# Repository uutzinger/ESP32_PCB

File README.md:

# ESP32 PCBs

Designed with KiCad by Urs Utzinger, February - June 2026.

- Full size battery operated ESP32-S3-Mini
- Minimial size ESP32-S3.
- Minimal size ESP32-C6, low power.

Based on S3/C6-mini modules.

<table style="width:100%; table-layout:fixed;">
  <tr>
    <td valign="bottom" style="width:33.3%; text-align:center;">
      
      <br>
      <b>ESP32-S3-MINI-1</b>
      <ul style="text-align:left; margin:8px auto; max-width:90%; list-style:none; padding-left:0;">
        <li>📡 Antenna</li>
        <li>🔋 Battery management</li>
        <li>📊 Battery gauge</li>
        <li>⚡ Dual supply power (ext 5V or USB 5V) </li>
        <li>⇄ USB-C</li>
        <li>🔗 QWIIC</li>
        <li>🌈 RGB LED</li>
        <li>🌡 Temperature sensor</li>
        <li>🔘 Bootmode, Reset buttons</li>
      </ul>
    </td>
    <td valign="top" style="width:33.3%; text-align:center;">
      
      <br>
      <b>ESP32-S3-MINI-1U</b>
      <ul style="text-align:left; margin:8px auto; max-width:90%; list-style:none; padding-left:0;">
        <li>⚡ Dual supply power (external 5V or USB 5V)</li>
        <li>⇄ USB-C</li>
        <li>🔗 QWIIC</li>
        <li>🌈 RGB LED</li>
        <li>🌡 Temperature sensor</li>
        <li>🔘 Bootmode, Reset buttons</li>
      </ul>
    </td>
    <td valign="top" style="width:33.3%; text-align:center;">
      
      <br>
      <b>ESP32-C6-MINI-1</b>
      <ul style="text-align:left; margin:8px auto; max-width:90%; list-style:none; padding-left:0;">
        <li>📡 Antenna</li>
        <li>🔋 Battery management</li>
        <li>📊 Battery gauge</li>
        <li>⇄ USB-C</li>
        <li>🌡 Temperature sensor</li>
        <li>🫨 Acceleromter</li>
        <li>no Buttons
      </ul>
    </td>
  </tr>
</table>

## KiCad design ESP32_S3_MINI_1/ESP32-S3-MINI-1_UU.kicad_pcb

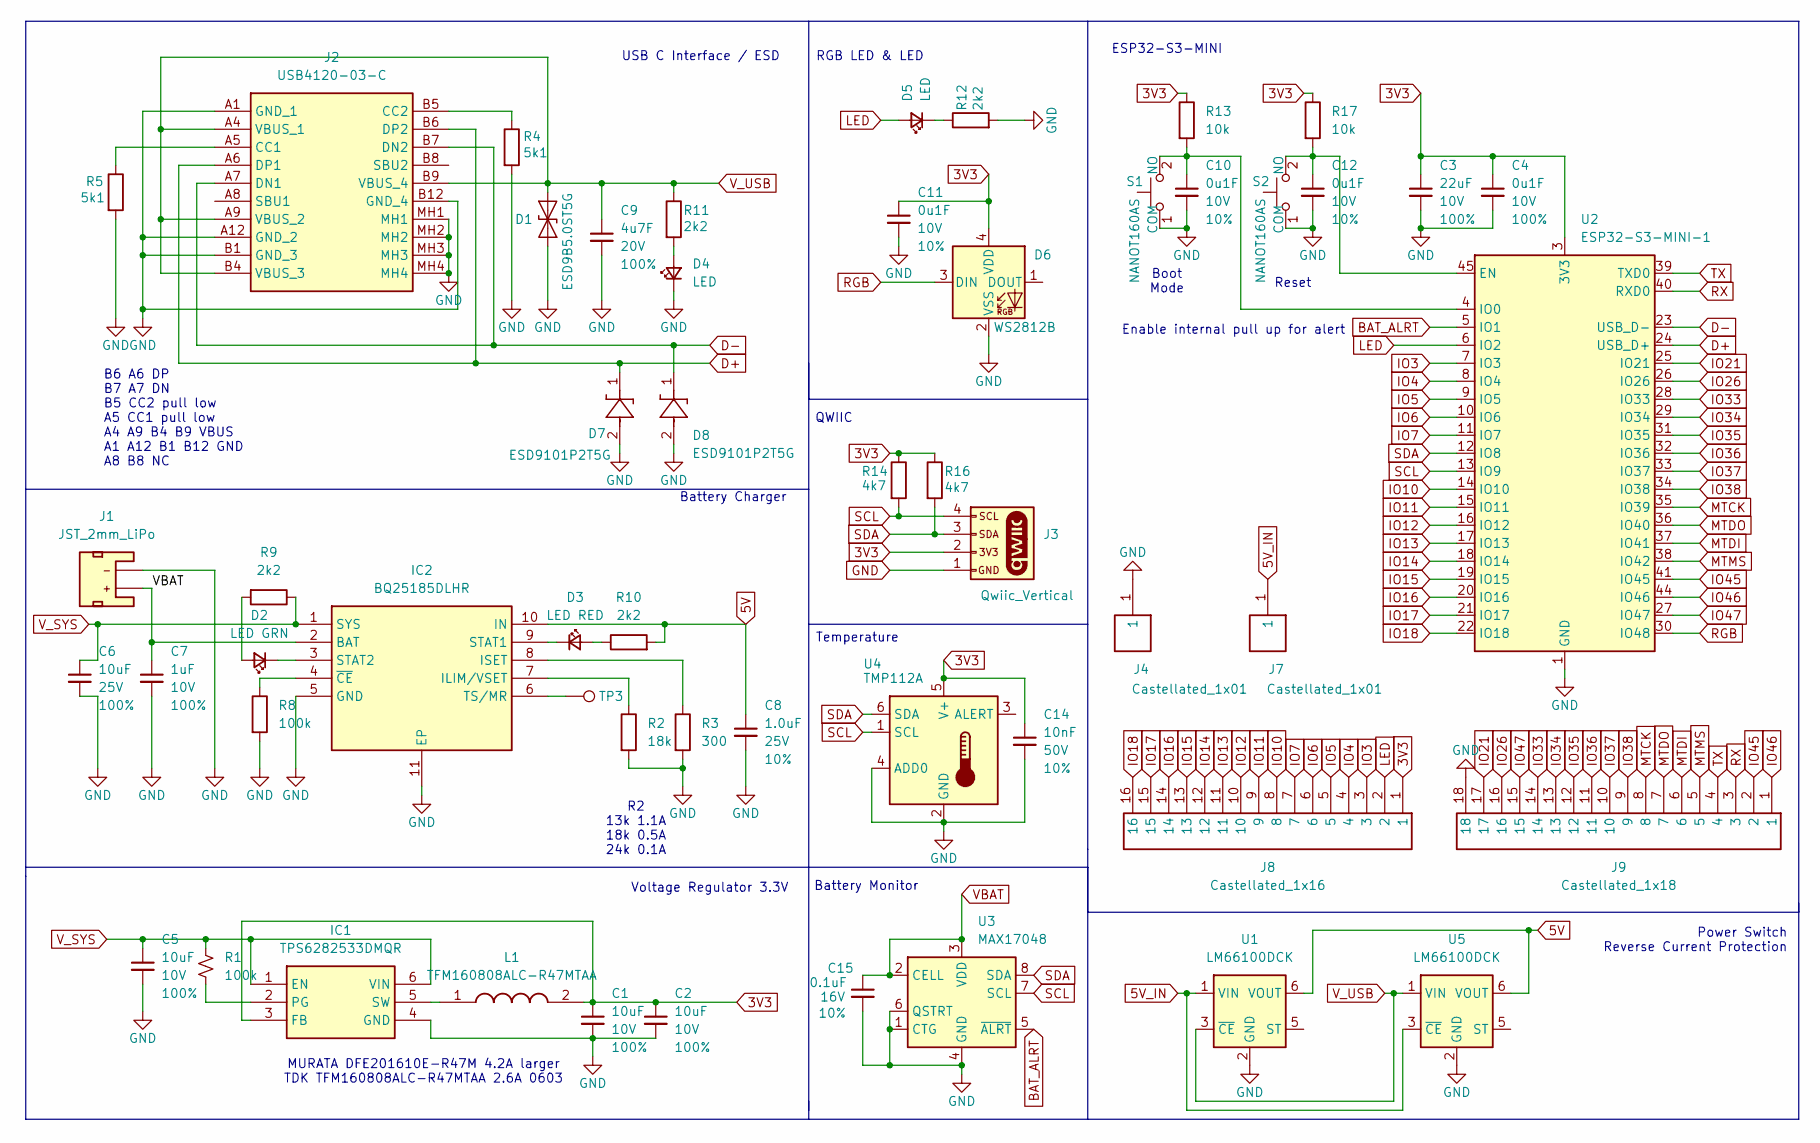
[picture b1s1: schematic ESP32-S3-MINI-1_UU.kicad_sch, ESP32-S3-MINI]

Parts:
C1, C2, C5: 10uF; C_0402_1005Metric; Voltage 10V; Tolerance 100%
C3: 22uF; C_0402_1005Metric; Voltage 10V; Tolerance 100%
C4: 0u1F; C_0402_1005Metric; Voltage 10V; Tolerance 100%
C6: 10uF; C_0402_1005Metric; Voltage 25V; Tolerance 100%
C7: 1uF; C_0402_1005Metric; Voltage 10V; Tolerance 100%
C8: 1.0uF; C_0402_1005Metric; Voltage 25V; Tolerance 10%
C9: 4u7F; C_0402_1005Metric; Voltage 20V; Tolerance 100%
C10, C11, C12: 0u1F; C_0402_1005Metric; Voltage 10V; Tolerance 10%
C14: 10nF; C_0402_1005Metric; Voltage 50V; Tolerance 10%
C15: 0.1uF; C_0402_1005Metric; Voltage 16V; Tolerance 10%
D1: ESD9B5.0ST5G; D_SOD-923
D2: LED GRN; LED_0402_1005Metric
D3: LED RED; LED_0402_1005Metric
D4, D5: LED; LED_0402_1005Metric
D6: WS2812B; WS2812_2020
D7, D8: ESD9101P2T5G; SODFL1006X40N; Manufacturer_Part_Number ESD9101P2T5G; Mouser Part Number 863-ESD9101P2T5G
IC1: TPS6282533DMQR; Manufacturer_Part_Number TPS6282533DMQR; Mouser Part Number 595-TPS6282533DMQR
IC2: BQ25185DLHR; SON40P220X200X80-11N; Manufacturer_Part_Number BQ25185DLHR; Mouser Part Number 595-BQ25185DLHR
J1: JST_2mm_LiPo; JST_1x02_P2.0mm_Horizontal_SMD
J2: USB4120-03-C; USB412003C; Manufacturer_Part_Number USB4120-03-C; Mouser Part Number 640-USB4120-03-C
J3: Qwiic_Vertical; JST_1x04_P1.0mm_Vertical_SMD
J4, J7: Castellated_1x01; Castellated_1x01_P2.54mm_D0.80mm
J8: Castellated_1x16; Castellated_1x16_P2.54mm_D0.80mm
J9: Castellated_1x18; Castellated_1x18_P2.54mm_D0.80mm
L1: TFM160808ALC-R47MTAA; INDC1608X75N; Manufacturer_Part_Number TFM160808ALC-R47MTAA; Mouser Part Number 810-TFM160808ALCR47A
R1, R8: 100k; R_0402_1005Metric
R2: 18k; R_0402_1005Metric
R3: 300; R_0402_1005Metric
R4, R5: 5k1; R_0402_1005Metric
R9, R10, R11, R12: 2k2; R_0402_1005Metric
R13, R17: 10k; R_0402_1005Metric
R14, R16: 4k7; R_0402_1005Metric
S1, S2: NANOT160AS; Mouser Part Number 611-NANOT160AS
TP3: TestPoint; TestPoint_Pad_1.0x1.0mm
U1, U5: LM66100DCK; SOT-363_SC-70-6
U2: ESP32-S3-MINI-1; ESP32-S2-MINI-1
U3: MAX17048; DFN-8_2x2mm_P0.5mm_EP1.2x0.8mm
U4: TMP112A; SOT-563

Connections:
3V3: C1.1, C2.1, C3.1, C4.1, C11.1, C14.1, D6.4 (VDD), IC1.3 (FB), J3.2, J8.1, L1.2, R13.1, R14.1, R16.1, R17.1, U2.3 (3V3), U4.5 (V+)
5V: C8.1, IC2.10 (IN), R10.2, U1.6 (VOUT), U5.6 (VOUT)
5V_IN: J7.1 (1_1), U1.1 (VIN), U5.3 (~CE)
BAT_ALRT: U2.5 (IO1), U3.5 (~ALRT)
D+: D7.1, J2.A6 (DP1), J2.B6 (DP2), U2.24 (USB_D+)
D-: D8.1, J2.A7 (DN1), J2.B7 (DN2), U2.23 (USB_D-)
GND: C1.2, C2.2, C3.2, C4.2, C5.2, C6.2, C7.2, C8.2, C9.2, C10.2, C11.2, C12.2, C14.2, C15.2, D1.2 (A2), D4.1 (K), D6.2 (VSS), D7.2, D8.2, IC1.4 (GND), IC2.5 (GND), IC2.11 (EP), J1.1 (-), J2.A1 (GND_1), J2.A12 (GND_2), J2.B1 (GND_3), J2.B12 (GND_4), J2.MH1, J2.MH2, J2.MH3, J2.MH4, J3.1, J4.1 (1_1), J9.18, R2.2, R3.2, R4.2, R5.2, R8.2, R12.2, S1.1 (COM), S2.1 (COM), U1.2 (GND), U2.1 (GND), U2.2 (GND), U2.42 (GND), U2.43 (GND), U2.46 (GND), U2.47 (GND), U2.48 (GND), U2.49 (GND), U2.50 (GND), U2.51 (GND), U2.52 (GND), U2.53 (GND), U2.54 (GND), U2.55 (GND), U2.56 (GND), U2.57 (GND), U2.58 (GND), U2.59 (GND), U2.60 (GND), U2.61 (GND), U2.62 (GND), U2.63 (GND), U2.64 (GND), U2.65 (GND), U3.1 (CTG), U3.4 (GND), U3.6 (QSTRT), U3.9 (GND), U4.2 (GND), U4.4 (ADD0), U5.2 (GND)
IO3: J8.3, U2.7 (IO3)
IO4: J8.4, U2.8 (IO4)
IO5: J8.5, U2.9 (IO5)
IO6: J8.6, U2.10 (IO6)
IO7: J8.7, U2.11 (IO7)
IO10: J8.8, U2.14 (IO10)
IO11: J8.9, U2.15 (IO11)
IO12: J8.10, U2.16 (IO12)
IO13: J8.11, U2.17 (IO13)
IO14: J8.12, U2.18 (IO14)
IO15: J8.13, U2.19 (IO15)
IO16: J8.14, U2.20 (IO16)
IO17: J8.15, U2.21 (IO17)
IO18: J8.16, U2.22 (IO18)
IO21: J9.17, U2.25 (IO21)
IO26: J9.16, U2.26 (IO26)
IO33: J9.14, U2.28 (IO33)
IO34: J9.13, U2.29 (IO34)
IO35: J9.12, U2.31 (IO35)
IO36: J9.11, U2.32 (IO36)
IO37: J9.10, U2.33 (IO37)
IO38: J9.9, U2.34 (IO38)
IO45: J9.2, U2.41 (IO45)
IO46: J9.1, U2.44 (IO46)
IO47: J9.15, U2.27 (IO47)
LED: D5.2 (A), J8.2, U2.6 (IO2)
MTCK: J9.8, U2.35 (IO39)
MTDI: J9.6, U2.37 (IO41)
MTDO: J9.7, U2.36 (IO40)
MTMS: J9.5, U2.38 (IO42)
unnamed: D2.2 (A), R9.2
unnamed: D2.1 (K), IC2.3 (STAT2)
unnamed: D3.2 (A), R10.1
unnamed: D3.1 (K), IC2.9 (STAT1)
unnamed: D4.2 (A), R11.2
unnamed: D5.1 (K), R12.1
unnamed: IC1.2 (PG), R1.1
unnamed: IC1.5 (SW), L1.1
unnamed: IC2.7 (ILIM/VSET), R2.1
unnamed: IC2.8 (ISET), R3.1
unnamed: IC2.6 (TS/MR), TP3.1 (1_1)
unnamed: IC2.4 (~CE), R8.1
unnamed: J2.A5 (CC1), R5.1
unnamed: J2.B5 (CC2), R4.1
unnamed: C10.1, R13.2, S1.2 (NO), U2.4 (IO0)
unnamed: C12.1, R17.2, S2.2 (NO), U2.45 (EN)
RGB: D6.3 (DIN), U2.30 (IO48)
RX: J9.3, U2.40 (RXD0)
SCL: J3.4, R14.2, U2.13 (IO9), U3.7 (SCL), U4.1 (SCL)
SDA: J3.3, R16.2, U2.12 (IO8), U3.8 (SDA), U4.6 (SDA)
TX: J9.4, U2.39 (TXD0)
VBAT: C7.1, C15.1, IC2.2 (BAT), J1.2 (+), U3.2 (CELL), U3.3 (VDD)
V_SYS: C5.1, C6.1, IC1.1 (EN), IC1.6 (VIN), IC2.1 (SYS), R1.2, R9.1
V_USB: C9.1, D1.1 (A1), J2.A4 (VBUS_1), J2.A9 (VBUS_2), J2.B4 (VBUS_3), J2.B9 (VBUS_4), R11.1, U1.3 (~CE), U5.1 (VIN)

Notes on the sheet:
Voltage Regulator 3.3V
Boot Mode
ESP32-S3-MINI
Battery Monitor
Power Switch Reverse Current Protection
MURATA DFE201610E-R47M 4.2A larger TDK TFM160808ALC-R47MTAA 2.6A 0603
Temperature
RGB LED & LED
Reset
R2 13k 1.1A 18k 0.5A 24k 0.1A
Battery Charger
Enable internal pull up for alert
B6 A6 DP B7 A7 DN B5 CC2 pull low A5 CC1 pull low A4 A9 B4 B9 VBUS A1 A12 B1 B12 GND A8 B8 NC
USB C Interface / ESD
QWIIC

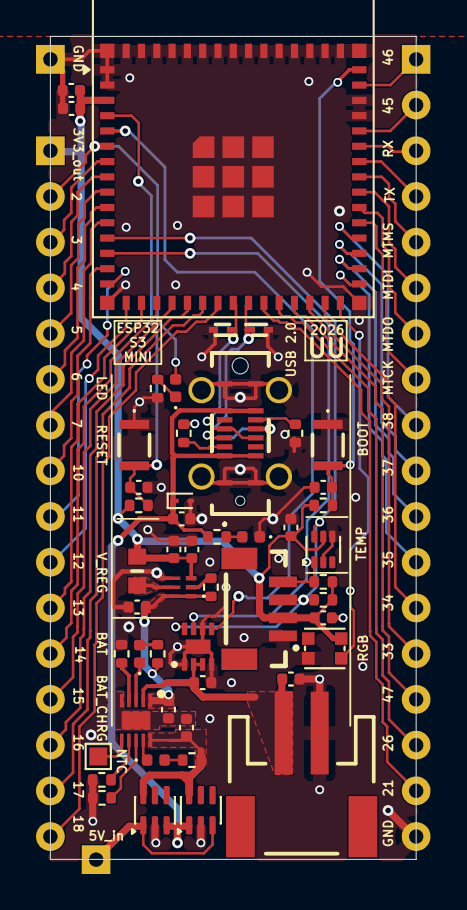
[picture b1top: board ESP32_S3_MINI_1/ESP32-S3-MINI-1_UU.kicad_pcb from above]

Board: 2 copper layers, 20.3 x 45.7 mm, 54 parts (0 on the bottom side), 61 nets.

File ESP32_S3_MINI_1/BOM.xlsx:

Id | Designator | Footprint | Quantity | Item | Manufacturer | Mfg Part # | Description/Value | Part # LCSC | LCSC | Cost LCSC |  | Part # Mouser | Mouser website | Cost Mouser
1 | C11,C12,C10,C15,C4 | C_0402_1005Metric | 5 | Capacitor | muRata | GRM155R71A104KA01D | 0u1F | C71687 | https://www.lcsc.com/product-detail/C71687.html?s_z=n_C71687 | 0.32 | 1.6
2 | C14 | C_0402_1005Metric | 1 | Capacitor | YAGEO | CC0402KRX7R6BB103 | 10nF | C541371 | https://www.lcsc.com/product-detail/C541371.html?s_z=n_C541371 | 0.13 | 0.13
3 | C3 | C_0402_1005Metric | 1 | Capacitor | muRata | GRM158R61A226ME15D | 22uF | C3845593 | https://www.lcsc.com/product-detail/C3845593.html?s_z=n_C3845593 | 0.57 | 0.57
4 | C5,C1,C2,C6 | C_0402_1005Metric | 4 | Capacitor | muRata | GRM155R61A106ME44D | 10uF | C77000 | https://www.lcsc.com/product-detail/C77000.html?s_z=n_C77000 | 0.58 | 2.32
5 | C7,C8 | C_0402_1005Metric | 2 | Capacitor | muRata | GCM155C71A105KE38D | 1uF | C126521 | https://www.lcsc.com/product-detail/C126521.html?s_z=n_C126521 | 0.96 | 1.92
6 | C9 | C_0402_1005Metric | 1 | Capacitor | muRata | GRM155R61A475KEAAD | 4u7F | C77004 | https://www.lcsc.com/product-detail/C77004.html?s_z=n_C77004 | 0.81 | 0.81
7 | D1 | D_SOD-923 | 1 | V_USB ESD | onSemi | ESD9B5.0ST5G | ESD9B5.0ST5G | C111566 | https://www.lcsc.com/product-detail/C111566.html?s_z=n_C111566 | 0.04 | 0.04 | 863-ESD9B5.0ST5G | https://www.mouser.com/ProductDetail/onsemi/ESD9B5.0ST5G?qs=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 | 0.1
8 | D2 | LED_0402_1005Metric | 1 | LED | Vishay | VLMG1500-GS08 | LED GRN | C511404 | https://www.lcsc.com/product-detail/C511404.html?s_z=n_C511404 | 0.19 | 0.19 | 78-VLMG1500-GS08 | https://www.mouser.com/ProductDetail/Vishay-Semiconductors/V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 | 0.34
9 | D3 | LED_0402_1005Metric | 1 | LED | Vishay | VLMS1500-GS08 | LED RED | C511370 | https://www.lcsc.com/product-detail/C511370.html?s_z=n_C511370 | 0.17 | 0.17 | 78-VLMS1500-GS08 | https://www.mouser.com/ProductDetail/Vishay-Semiconductors/V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 | 0.24
10 | D4,D5 | LED_0402_1005Metric | 2 | LED | Vishay | VLMB1500-GS08 | LED BLUE | C511042 | https://www.lcsc.com/product-detail/C511042.html?s_z=n_C511042 | 0.2 | 0.4 | 78-VLMB1500-GS08 | https://www.mouser.com/ProductDetail/Vishay-Semiconductors/V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 | 0.27
11 | D6 | WS2812_2020 | 1 | RGB LED | Worldsemi | WS2812B-2020 | WS2812B | C965555 | https://www.lcsc.com/product-detail/C965555.html?s_z=n_C965555 | 0.45 | 0.45
12 | D7,D8 | D_SOD-923 | 2 | USB ESD | Onsemi | ESD9101P2T5G | ESD9101P2T5G | C41348159 | https://www.lcsc.com/product-detail/C41348159.html?s_z=n_ESD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 | 0.56 | 1.12 | 863-ESD9101P2T5G | https://www.mouser.com/ProductDetail/onsemi/ESD9101P2T5G?qs=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 | 0.26
13 | IC1 | TPS6282533DMQR | 1 | Volt Regulator | TI | TPS6282533DMQR | TPS6282533DMQR | C3189971 | https://www.lcsc.com/product-detail/C3189971.html?s_z=n_C3189971 | 1.17 | 1.17 | 595-TPS6282533DMQR | https://www.mouser.com/ProductDetail/Texas-Instruments/TPS62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 | 1.25
14 | IC2 | SON40P220X200X80-11N | 1 | Bat Charger | TI | BQ25185DLHR | BQ25185DLHR | C19725033 | https://www.lcsc.com/product-detail/C19725033.html?s_z=n_C19725033 | 1.9 | 1.9 | 595-BQ25185DLHR | https://www.mouser.com/ProductDetail/Texas-Instruments/BQ251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 | 2.03
15 | J1 | JST_1x02_P2.0mm_Horizontal_SMD | 1 | Connector | JST | JST S2B-PH-SM4-TB | JST_2mm_LiPo, SMF, right angle | C295747 | https://www.lcsc.com/product-detail/C295747.html?s_z=n_C295747 | 0.2 | 0.2 | 306-S2BPHSM4TBLFSN | https://www.mouser.com/ProductDetail/JST-Commercial/S2B-PH-S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 | 0.49
16 | J2 | USB412003C | 1 | Connector | GCT | USB4120-03-C | USB4120-03-C | C3445864 | https://www.lcsc.com/product-detail/C3445864.html?s_z=n_C3445864 | 1.31 | 1.31 | 640-USB4120-03-C | https://www.mouser.com/ProductDetail/GCT/USB4120-03-C?qs=KUo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 | 0.86
17 | J3 | JST_1x04_P1.0mm_Vertical_SMD | 1 | Connector | BOOMELE | 1.0T-4PLTPZ | Qwiic_Vertical | C2974722 | https://www.lcsc.com/product-detail/C2974722.html | 0.65 | 0.65
18 | J7,J4 | Castellated_1x01_P2.54mm_D0.80mm | 1 | Connector | D.N.P. | D.N.P. | Castellated_1x01 |  | Do No Populate
19 | J8 | Castellated_1x16_P2.54mm_D0.80mm | 1 | Connector | D.N.P. | D.N.P. | Castellated_1x16 |  | Do No Populate
20 | J9 | Castellated_1x18_P2.54mm_D0.80mm | 1 | Connector | D.N.P. | D.N.P. | Castellated_1x18 |  | Do No Populate
21 | L1 | C_0603 | 1 | Inductor | TDK | TFM160808ALC-R47MTAA | TFM160808ALC-R47MTAA | C695609 | https://www.lcsc.com/product-detail/C695609.html?s_z=n_C695609 | 0.13 | 0.13 | 810-TFM160808ALCR47A | https://www.mouser.com/ProductDetail/TDK/TFM160808ALC-R47MTA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 | 0.25
22 | R1,R8 | R_0402_1005Metric | 2 | Resistor | YAGEO | RC0402FR-07100KL | 100k | C60491 | https://www.lcsc.com/product-detail/C60491.html?s_z=n_C60491 | 0.08 | 0.16
23 | R14,R16 | R_0402_1005Metric | 2 | Resistor | YAGEO | RC0402FR-074K7L | 4k7 | C105871 | https://www.lcsc.com/product-detail/C105871.html?s_z=n_C105871 | 0.08 | 0.16
24 | R15 | R_0402_1005Metric | 1 | Resistor | YAGEO | RC0402FR-07330RL | 330 | C105875 | https://www.lcsc.com/product-detail/C105875.html?s_z=n_C105875 | 0.08 | 0.08
25 | R2 | R_0402_1005Metric | 1 | Resistor | YAGEO | RC0402FR-0718KL | 18k | C138044 | https://www.lcsc.com/product-detail/C138044.html?s_z=n_C138044 | 0.08 | 0.08
26 | R3 | R_0402_1005Metric | 1 | Resistor | YAGEO | RC0402FR-07300RL | 300 | C138010 | https://www.lcsc.com/product-detail/C138010.html?s_z=n_C138010 | 0.08 | 0.08
27 | R4,R5 | R_0402_1005Metric | 2 | Resistor | YAGEO | RC0402FR-075K1L | 5k1 | C105872 | https://www.lcsc.com/product-detail/C105872.html?s_z=n_C105872 | 0.08 | 0.16
28 | R9,R12,R10,R11 | R_0402_1005Metric | 4 | Resistor | YAGEO | RC0402FR-072K2L | 2k2 | C114762 | https://www.lcsc.com/product-detail/C114762.html?s_z=n_C114762 | 0.09 | 0.36
29 | S1,S2 | NANOT160AS | 2 | Micro Switch | C&K | NANOT160AS | NANOT160AS | C2760981 | https://www.lcsc.com/product-detail/C2760981.html?s_z=n_C2760981 | 1.72 | 3.44 | 611-NANOT160AS | https://www.mouser.com/ProductDetail/CK/NANOT160AS?qs=OlC7Aq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 | 0.4
30 | R13,R17 | R_0402_1005Metric | 2 | Resistor | YAGEO | RC0402FR-0710KL | 10k | C60490 | https://www.lcsc.com/product-detail/C60490.html?s_z=n_C60490 | 0.08 | 0.16
31 | TH1 | R_0402_1005Metric | 1 | Thermistor | MURATA | NCP15XH103F03RC | 10k NTC | C77131 | https://www.lcsc.com/product-detail/C77131.html?s_z=n_C77131 | 0.01 | 0.01
32 | U2 | ESP32-S2-MINI-1 SMD | 1 | MCU Module | Espressif | ESP32-S3-MINI-1-N8 | ESP32 S3 Mini 1 8MB Flash | C2913206 | https://www.lcsc.com/product-detail/C2913206.html?s_z=n_C2913206 | 4.6185 | 4.6185
33 | U3 | DFN-8_2x2mm_P0.5mm_EP1.2x0.8mm | 1 | Bat Gauge | Maxim | MAXIM MAX17048G+T10 | MAX17048 | C2682616 | https://www.lcsc.com/product-detail/C2682616.html?s_z=n_C2682616 | 2.66 | 2.66 | 700-MAX17048G+T10 | https://www.mouser.com/ProductDetail/Analog-Devices-Maxim-In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 | 5.77
34 | U4 | SOT-563 | 1 | Temp Sensor | Texas Instruments | TMP102AIDRLR | TMP102 | C99269 | https://www.lcsc.com/product-detail/C99269.html?s_z=n_C99269 | 0.22 | 0.22 | 595-TMP102AQDRLRQ1 | https://www.mouser.com/ProductDetail/Texas-Instruments/TMP10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 | 1.52
35 | U5,U1 | SOT-363_SC-70-6 | 2 | Ideal Diode | Texas Instruments | LM66100DCK | Ideal Diode, Input Polarity Prot. | C2869734 | https://www.lcsc.com/product-detail/C2869734.html?s_z=n_C2869734 | 0.88 | 1.76 | 595-LM66100DCKT | https://www.mouser.com/ProductDetail/Texas-Instruments/LM661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 | 0.85
 |  |  |  |  |  |  |  |  |  |  | 29.0285

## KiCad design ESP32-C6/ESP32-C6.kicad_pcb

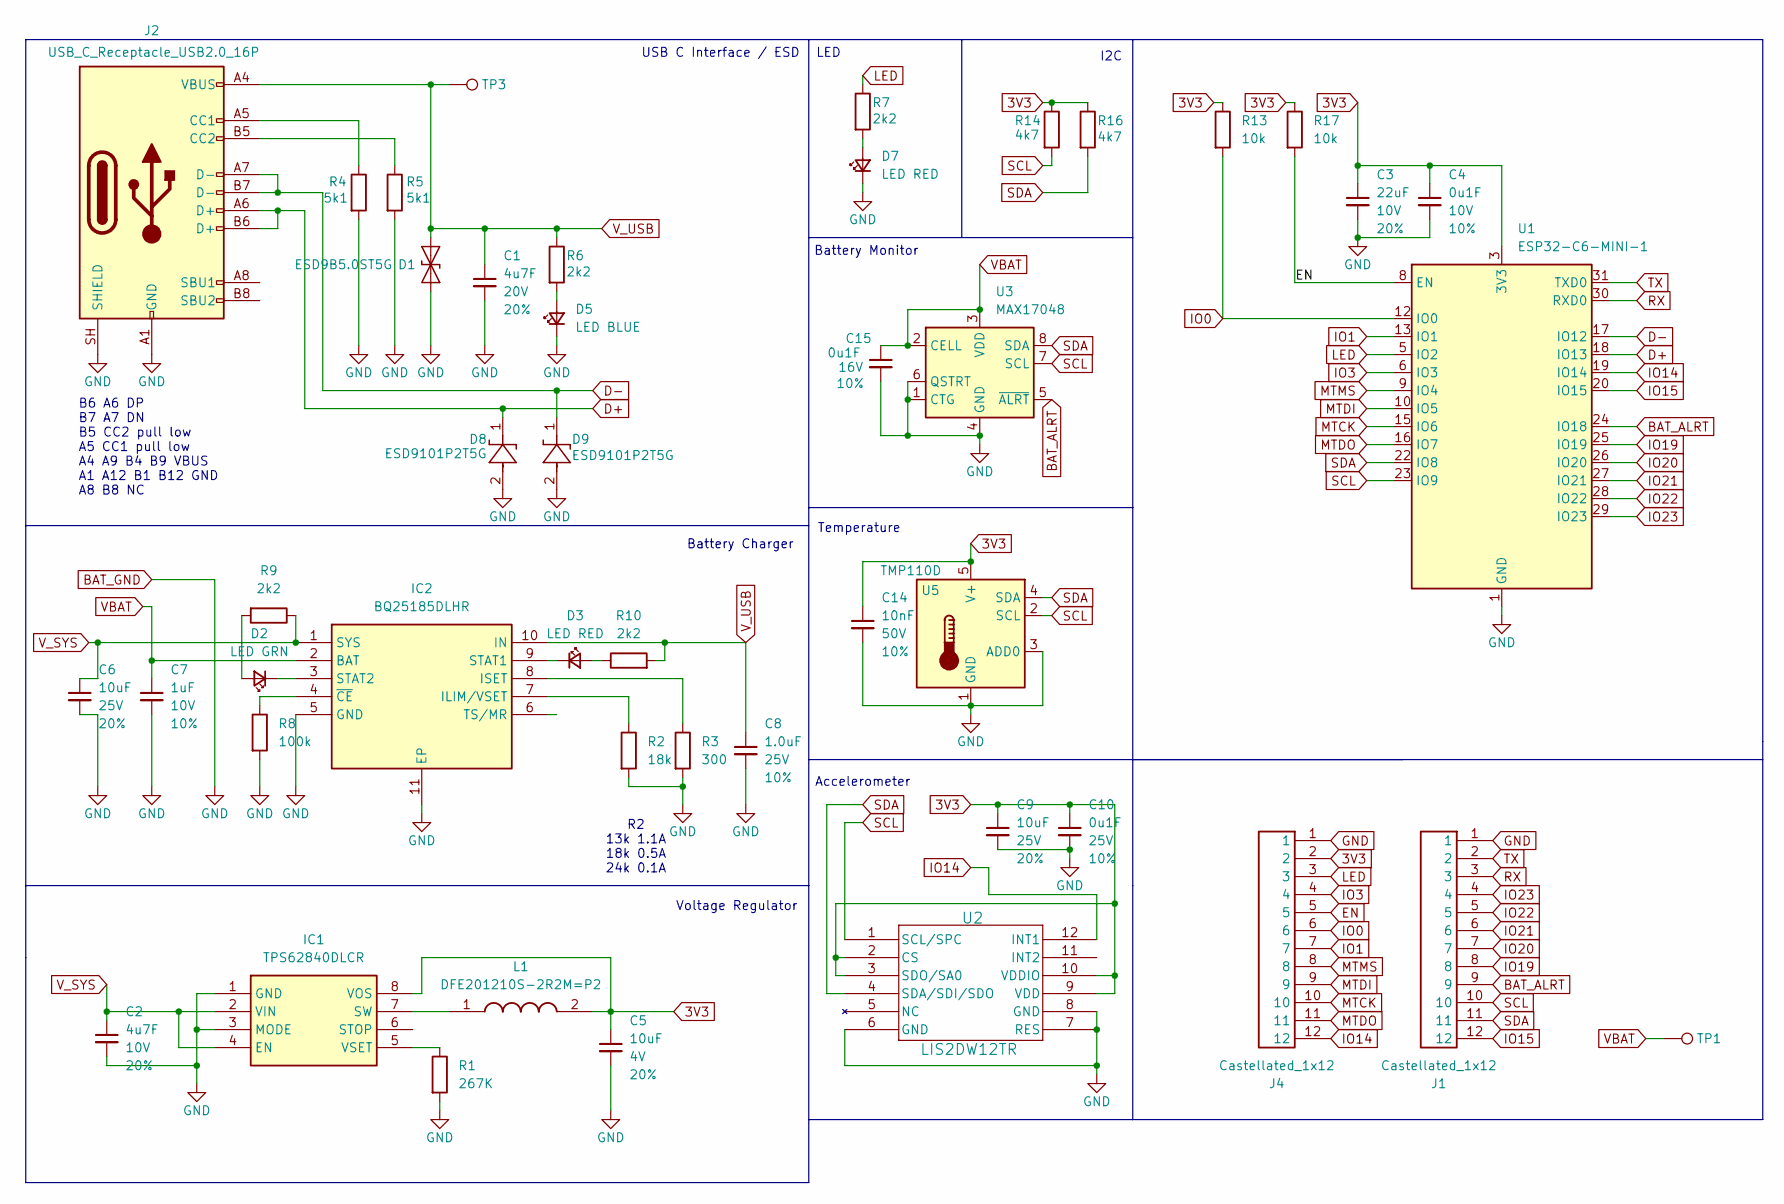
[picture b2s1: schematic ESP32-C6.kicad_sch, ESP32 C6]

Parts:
C1: 4u7F; C_0402_1005Metric; Voltage 20V; Tolerance 20%
C2: 4u7F; C_0402_1005Metric; Voltage 10V; Tolerance 20%
C3: 22uF; C_0402_1005Metric; Voltage 10V; Tolerance 20%
C4: 0u1F; C_0402_1005Metric; Voltage 10V; Tolerance 10%
C5: 10uF; C_0402_1005Metric; Voltage 4V; Tolerance 20%
C6, C9: 10uF; C_0402_1005Metric; Voltage 25V; Tolerance 20%
C7: 1uF; C_0402_1005Metric; Voltage 10V; Tolerance 10%
C8: 1.0uF; C_0402_1005Metric; Voltage 25V; Tolerance 10%
C10: 0u1F; C_0402_1005Metric; Voltage 25V; Tolerance 10%
C14: 10nF; C_0201_0603Metric; Voltage 50V; Tolerance 10%
C15: 0u1F; C_0402_1005Metric; Voltage 16V; Tolerance 10%
D1: ESD9B5.0ST5G; D_SOD-923
D2: LED GRN; LED_0402_1005Metric
D3, D7: LED RED; LED_0402_1005Metric
D5: LED BLUE; LED_0402_1005Metric
D8, D9: ESD9101P2T5G; SODFL1006X40N; Manufacturer_Part_Number ESD9101P2T5G; Mouser Part Number 863-ESD9101P2T5G
IC1: TPS62840DLCR; SON50P150X200X100-8N-D; Manufacturer_Part_Number TPS62840DLCR; Mouser Part Number 595-TPS62840DLCR
IC2: BQ25185DLHR; SON40P220X200X80-11N; Manufacturer_Part_Number BQ25185DLHR; Mouser Part Number 595-BQ25185DLHR
J1, J4: Castellated_1x12; Castellated_1x12_P2.54mm_D0.80mm
J2: USB_C_Receptacle_USB2.0_16P; USB_C_Receptacle_GCT_USB4105-xx-A_16P_TopMnt_Horizontal
L1: DFE201210S-2R2M=P2; DFE201210S1R0MP2; Manufacturer_Part_Number DFE201210S-2R2M=P2; Mouser Part Number 81-DFE201210S-2R2MP2
R1: 267K; R_0402_1005Metric
R2: 18k; R_0402_1005Metric
R3: 300; R_0402_1005Metric
R4, R5: 5k1; R_0402_1005Metric
R6, R7, R9, R10: 2k2; R_0402_1005Metric
R8: 100k; R_0402_1005Metric
R13, R17: 10k; R_0402_1005Metric
R14, R16: 4k7; R_0402_1005Metric
TP1, TP3: TestPoint; TestPoint_Pad_1.5x1.5mm
U1: ESP32-C6-MINI-1
U2: LIS2DW12TR; LGA-12_2X2X0P7_STM
U3: MAX17048; DFN-8_2x2mm_P0.5mm_EP1.2x0.8mm
U5: TMP110D; Texas_X2SON-5_0.8x0.8mm_P0.48mm

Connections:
3V3: C3.1, C4.1, C5.1, C9.1, C10.1, C14.1, IC1.8 (VOS), J4.2, L1.2, R13.1, R14.1, R16.1, R17.1, U1.3 (3V3), U2.2 (CS), U2.3 (SDO/SA0), U2.9 (VDD), U2.10 (VDDIO), U5.5 (V+)
BAT_ALRT: J1.9, U1.24 (IO18), U3.5 (~ALRT)
BAT_GND: C1.2, C2.2, C3.2, C4.2, C5.2, C6.2, C7.2, C8.2, C9.2, C10.2, C14.2, C15.2, D1.2 (A2), D5.1 (K), D7.1 (K), D8.2, D9.2, IC1.1 (GND), IC1.3 (MODE), IC2.5 (GND), IC2.11 (EP), J1.1, J2.A1 (GND), J2.A12 (GND), J2.B1 (GND), J2.B12 (GND), J2.SH (SHIELD), J4.1, R1.2, R2.2, R3.2, R4.2, R5.2, R8.2, U1.1 (GND), U1.2 (GND), U1.11 (GND), U1.14 (GND), U1.36 (GND), U1.37 (GND), U1.38 (GND), U1.39 (GND), U1.40 (GND), U1.41 (GND), U1.42 (GND), U1.43 (GND), U1.44 (GND), U1.45 (GND), U1.46 (GND), U1.47 (GND), U1.48 (GND), U1.49 (GND), U1.50 (GND), U1.51 (GND), U1.52 (GND), U1.53 (GND), U2.6 (GND), U2.7 (RES), U2.8 (GND), U3.1 (CTG), U3.4 (GND), U3.6 (QSTRT), U3.9 (GND), U5.1 (GND), U5.3 (ADD0)
D+: D8.1, J2.A6 (D+), J2.B6 (D+), U1.18 (IO13)
D-: D9.1, J2.A7 (D-), J2.B7 (D-), U1.17 (IO12)
EN: J4.5, R17.2, U1.8 (EN)
IO0: J4.6, R13.2, U1.12 (IO0)
IO1: J4.7, U1.13 (IO1)
IO3: J4.4, U1.6 (IO3)
IO14: J4.12, U1.19 (IO14), U2.12 (INT1)
IO15: J1.12, U1.20 (IO15)
IO19: J1.8, U1.25 (IO19)
IO20: J1.7, U1.26 (IO20)
IO21: J1.6, U1.27 (IO21)
IO22: J1.5, U1.28 (IO22)
IO23: J1.4, U1.29 (IO23)
LED: J4.3, R7.1, U1.5 (IO2)
MTCK: J4.10, U1.15 (IO6)
MTDI: J4.9, U1.10 (IO5)
MTDO: J4.11, U1.16 (IO7)
MTMS: J4.8, U1.9 (IO4)
unnamed: D2.2 (A), R9.2
unnamed: D2.1 (K), IC2.3 (STAT2)
unnamed: D3.2 (A), R10.1
unnamed: D3.1 (K), IC2.9 (STAT1)
unnamed: D5.2 (A), R6.2
unnamed: D7.2 (A), R7.2
unnamed: IC1.7 (SW), L1.1
unnamed: IC1.5 (VSET), R1.1
unnamed: IC2.7 (ILIM/VSET), R2.1
unnamed: IC2.8 (ISET), R3.1
unnamed: IC2.4 (~CE), R8.1
unnamed: J2.A5 (CC1), R4.1
unnamed: J2.B5 (CC2), R5.1
RX: J1.3, U1.30 (RXD0)
SCL: J1.10, R14.2, U1.23 (IO9), U2.1 (SCL/SPC), U3.7 (SCL), U5.2 (SCL)
SDA: J1.11, R16.2, U1.22 (IO8), U2.4 (SDA/SDI/SDO), U3.8 (SDA), U5.4 (SDA)
TX: J1.2, U1.31 (TXD0)
VBAT: C7.1, C15.1, IC2.2 (BAT), TP1.1 (1_1), U3.2 (CELL), U3.3 (VDD)
V_SYS: C2.1, C6.1, IC1.2 (VIN), IC1.4 (EN), IC2.1 (SYS), R9.1
V_USB: C1.1, C8.1, D1.1 (A1), IC2.10 (IN), J2.A4 (VBUS), J2.A9 (VBUS), J2.B4 (VBUS), J2.B9 (VBUS), R6.1, R10.2, TP3.1 (1_1)

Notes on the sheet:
Accelerometer
B6 A6 DP B7 A7 DN B5 CC2 pull low A5 CC1 pull low A4 A9 B4 B9 VBUS A1 A12 B1 B12 GND A8 B8 NC
Battery Monitor
Voltage Regulator
I2C
LED
Battery Charger
Temperature
R2 13k 1.1A 18k 0.5A 24k 0.1A
USB C Interface / ESD

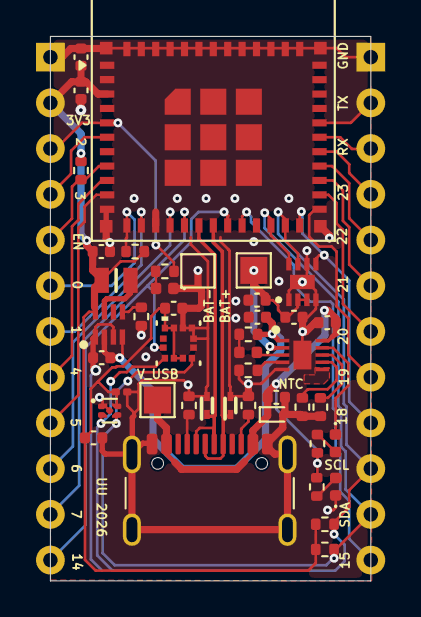
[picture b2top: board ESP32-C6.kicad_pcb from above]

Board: 2 copper layers, 17.8 x 30.2 mm, 45 parts (0 on the bottom side), 41 nets.

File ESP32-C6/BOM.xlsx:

Item # | *Designator | *Package/Footprint | *Qty | Item | Manufacturer | *Mfg Part # | Description / Value | Part # LCSC | LCSC Weblink | LSCS $ | Cost LCSC | Part # Mouser | Mouser Weblink | Mouser $
 | C1,C2 | C_0402_1005Metric | 2 | Capacitor | muRata | GRM155R61A475KEAAD | 4u7F | C77004 | https://www.lcsc.com/product-detail/C77004.html?s_z=n_C77004 | 0.81 | 1.62
 | C14 | C_0201_0603Metric | 1 | Capacitor | muRata | GRM033R71E103KE14D | 10nF | C85930 | https://www.lcsc.com/product-detail/C85930.html | 0.22 | 0.22
 | C10,C15,C4 | C_0402_1005Metric | 2 | Capacitor | muRata | GRM155R71H104KE14 | 0u1F | C77020 | https://www.lcsc.com/product-detail/C77020.htm | 0.33 | 0.66
 | C3 | C_0402_1005Metric | 1 | Capacitor | muRata | GRM158R61A226ME15D | 22uF | C3845593 | https://www.lcsc.com/product-detail/C3845593.html?s_z=n_C3845593 | 0.57 | 0.57
 | C6,C5, C9 | C_0402_1005Metric | 3 | Capacitor | muRata | GRM155R61A106ME44D | 10uF | C77000 | https://www.lcsc.com/product-detail/C77000.html?s_z=n_C77000 | 0.58 | 1.74
 | C7,C8 | C_0402_1005Metric | 2 | Capacitor | muRata | GRM155R61E105KA12 | 1uF | C77009 | https://www.lcsc.com/product-detail/C77009.html | 0.69 | 1.38
 | D1 | D_SOD-923 | 1 | ESD9B5.0ST5G | onSemi | ESD9B5.0ST5G | ESD9B5.0ST5G | C111566 | https://www.lcsc.com/product-detail/C111566.html?s_z=n_C111566 | 0.04 | 0.04
 | D2 | LED_0402_1005Metric | 1 | LED GRN | TOGIALED | TJ-S1005CL4T5ALC2G-A5 | LED GREEN | C917188 | https://www.lcsc.com/product-detail/C917188.html | 0.66
 | D3 | LED_0402_1005Metric | 1 | LED RED | TOGIALED | TJ-S1005SW4TGLC2R-A5 | LED RED | C273598 | https://www.lcsc.com/product-detail/C273598.html | 0.41 | 0.41
 | D7 | LED_0402_1005Metric | 1 | LED WHITE | TOGIALED | TJ-S1005CL4T5ALC3D | LED WHITE | C917191 | https://www.lcsc.com/product-detail/C917191.html | 0.48
 | D5 | LED_0402_1005Metric | 1 | LED BLUE | Vishay | VLMB1500-GS08 | LED BLUE | C511042 | https://www.lcsc.com/product-detail/C511042.html?s_z=n_C511042 | 0.2
 | D8,D9 | D_SOD-923 | 2 | ESD9101P2T5G | onSemi | ESD9101P2T5G | ESD9101P2T5G | C41348159 | https://www.lcsc.com/product-detail/C41348159.html?s_z=n_ESD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 | 0.56
 | IC1 | SON50P150X200X100-8N-D | 1 | TPS62840DLCR
 | IC2 | SON40P220X200X80-11N | 1 | BQ25185DLHR
 | J1,J4 | Castellated_1x12_P2.54mm_D0.80mm | 2 | Castellated_1x12
 | J2 |  | 1 | USB_C_Receptacle_USB2.0_16P |  | USB_C_Receptacle_GCT_USB4105-xx-A_16P_TopMnt_Horizontal
 | L1 | DFE201210S1R0MP2 | 1 | Inductor |  | DFE201210S-2R2M=P2
 | R1 | R_0402_1005Metric | 1 | 267K
 | R14,R16 | R_0402_1005Metric | 2 | 4k7
 | R17,R13 | R_0402_1005Metric | 2 | 10k
 | R2 | R_0402_1005Metric | 1 | 18k
 | R3 | R_0402_1005Metric | 1 | 300
 | R5,R4 | R_0402_1005Metric | 2 | 5k1
 | R7,R10,R6,R9 | R_0402_1005Metric | 4 | 2k2
 | R8 | R_0402_1005Metric | 1 | 100k
28 | TP1 | TestPoint_Pad_1.5x1.5mm | 1 | TestPoint
29 | TP3 | TestPoint_Pad_1.5x1.5mm | 1 | TestPoint
 | U1 | ESP32-C6-MINI-1 | 1 | MCU Module | Espressif Systems
 | U2 | LGA-12_2X2X0P7_STM | 1 | LIS2DW12TR
 | U3 | DFN-8_2x2mm_P0.5mm_EP1.2x0.8mm | 1 | MAX17048
 | U5 | Texas_X2SON-5_0.8x0.8mm_P0.48mm | 1 | TMP110D

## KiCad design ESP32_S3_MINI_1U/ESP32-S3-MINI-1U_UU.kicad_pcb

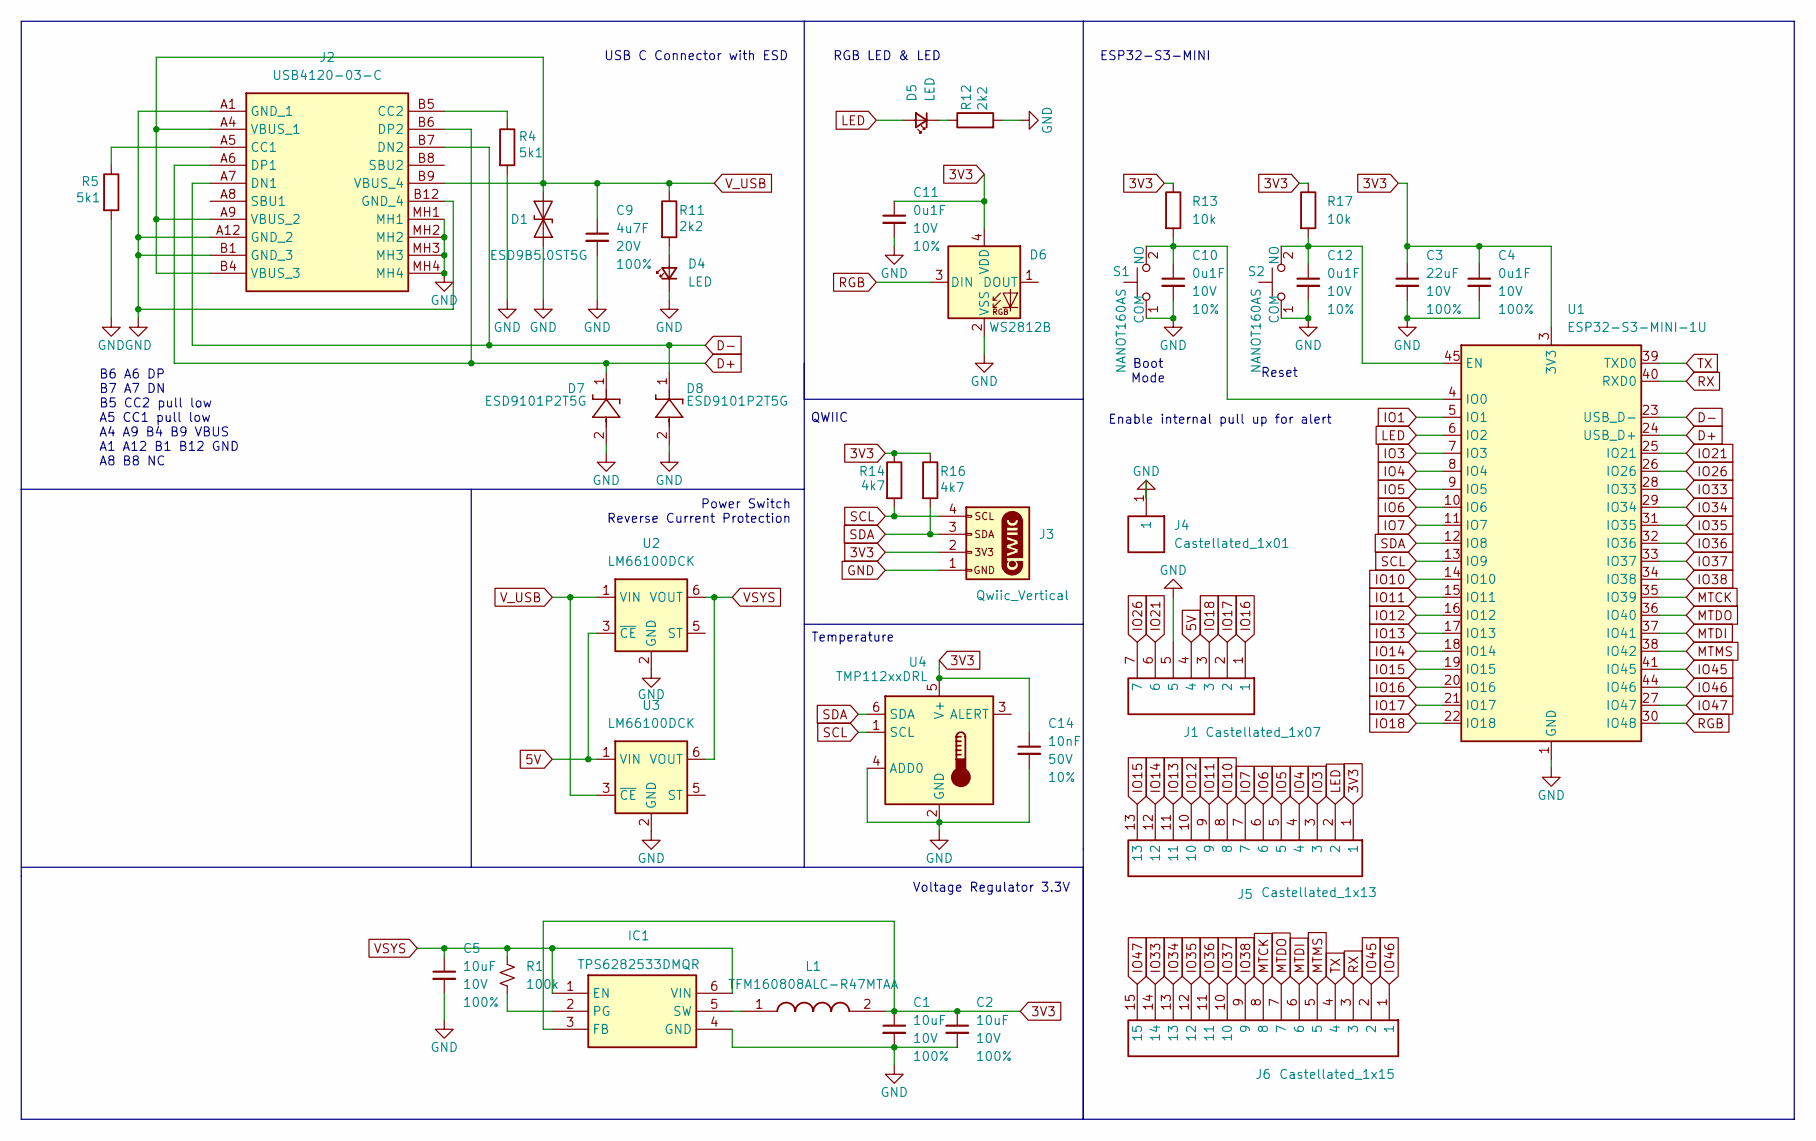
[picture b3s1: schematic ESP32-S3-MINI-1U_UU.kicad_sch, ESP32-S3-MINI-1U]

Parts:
C1, C2, C5: 10uF; C_0402_1005Metric; Voltage 10V; Tolerance 100%
C3: 22uF; C_0402_1005Metric; Voltage 10V; Tolerance 100%
C4: 0u1F; C_0402_1005Metric; Voltage 10V; Tolerance 100%
C9: 4u7F; C_0402_1005Metric; Voltage 20V; Tolerance 100%
C10, C11, C12: 0u1F; C_0402_1005Metric; Voltage 10V; Tolerance 10%
C14: 10nF; C_0402_1005Metric; Voltage 50V; Tolerance 10%
D1: ESD9B5.0ST5G; SODFL1006X40N
D4, D5: LED; LED_0402_1005Metric
D6: WS2812B; WS2812_2020
D7, D8: ESD9101P2T5G; SODFL1006X40N; Manufacturer_Part_Number ESD9101P2T5G; Mouser Part Number 863-ESD9101P2T5G
IC1: TPS6282533DMQR; Manufacturer_Part_Number TPS6282533DMQR; Mouser Part Number 595-TPS6282533DMQR
J1: Castellated_1x07; Castellated_1x07_P2.54mm_D0.80mm
J2: USB4120-03-C; USB412003C; Manufacturer_Part_Number USB4120-03-C; Mouser Part Number 640-USB4120-03-C
J3: Qwiic_Vertical; JST_1x04_P1.0mm_Vertical_SMD
J4: Castellated_1x01; Castellated_1x01_P2.54mm_D0.80mm
J5: Castellated_1x13; Castellated_1x13_P2.54mm_D0.80mm
J6: Castellated_1x15; Castellated_1x15_P2.54mm_D0.80mm
L1: TFM160808ALC-R47MTAA; INDC1608X75N; Manufacturer_Part_Number TFM160808ALC-R47MTAA; Mouser Part Number 810-TFM160808ALCR47A
R1: 100k; R_0402_1005Metric
R4, R5: 5k1; R_0402_1005Metric
R11, R12: 2k2; R_0402_1005Metric
R13, R17: 10k; R_0402_1005Metric
R14, R16: 4k7; R_0402_1005Metric
S1, S2: NANOT160AS; Mouser Part Number 611-NANOT160AS
U1: ESP32-S3-MINI-1U; ESP32-S2-MINI-1U
U2, U3: LM66100DCK; SOT-363_SC-70-6
U4: TMP112xxDRL; SOT-563

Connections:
3V3: C1.1, C2.1, C3.1, C4.1, C11.1, C14.1, D6.4 (VDD), IC1.3 (FB), J3.2, J5.1, L1.2, R13.1, R14.1, R16.1, R17.1, U1.3 (3V3), U4.5 (V+)
5V: J1.4, U2.3 (~CE), U3.1 (VIN)
D+: D7.1, J2.A6 (DP1), J2.B6 (DP2), U1.24 (USB_D+)
D-: D8.1, J2.A7 (DN1), J2.B7 (DN2), U1.23 (USB_D-)
GND: C1.2, C2.2, C3.2, C4.2, C5.2, C9.2, C10.2, C11.2, C12.2, C14.2, D1.2 (A2), D4.1 (K), D6.2 (VSS), D7.2, D8.2, IC1.4 (GND), J1.5, J2.A1 (GND_1), J2.A12 (GND_2), J2.B1 (GND_3), J2.B12 (GND_4), J2.MH1, J2.MH2, J2.MH3, J2.MH4, J3.1, J4.1 (1_1), R4.2, R5.2, R12.2, S1.1 (COM), S2.1 (COM), U1.1 (GND), U1.2 (GND), U1.42 (GND), U1.43 (GND), U1.46 (GND), U1.47 (GND), U1.48 (GND), U1.49 (GND), U1.50 (GND), U1.51 (GND), U1.52 (GND), U1.53 (GND), U1.54 (GND), U1.55 (GND), U1.56 (GND), U1.57 (GND), U1.58 (GND), U1.59 (GND), U1.60 (GND), U1.61 (GND), U1.62 (GND), U1.63 (GND), U1.64 (GND), U1.65 (GND), U2.2 (GND), U3.2 (GND), U4.2 (GND), U4.4 (ADD0)
IO1: U1.5 (IO1)
IO3: J5.3, U1.7 (IO3)
IO4: J5.4, U1.8 (IO4)
IO5: J5.5, U1.9 (IO5)
IO6: J5.6, U1.10 (IO6)
IO7: J5.7, U1.11 (IO7)
IO10: J5.8, U1.14 (IO10)
IO11: J5.9, U1.15 (IO11)
IO12: J5.10, U1.16 (IO12)
IO13: J5.11, U1.17 (IO13)
IO14: J5.12, U1.18 (IO14)
IO15: J5.13, U1.19 (IO15)
IO16: J1.1, U1.20 (IO16)
IO17: J1.2, U1.21 (IO17)
IO18: J1.3, U1.22 (IO18)
IO21: J1.6, U1.25 (IO21)
IO26: J1.7, U1.26 (IO26)
IO33: J6.14, U1.28 (IO33)
IO34: J6.13, U1.29 (IO34)
IO35: J6.12, U1.31 (IO35)
IO36: J6.11, U1.32 (IO36)
IO37: J6.10, U1.33 (IO37)
IO38: J6.9, U1.34 (IO38)
IO45: J6.2, U1.41 (IO45)
IO46: J6.1, U1.44 (IO46)
IO47: J6.15, U1.27 (IO47)
LED: D5.2 (A), J5.2, U1.6 (IO2)
MTCK: J6.8, U1.35 (IO39)
MTDI: J6.6, U1.37 (IO41)
MTDO: J6.7, U1.36 (IO40)
MTMS: J6.5, U1.38 (IO42)
unnamed: D4.2 (A), R11.2
unnamed: D5.1 (K), R12.1
unnamed: IC1.2 (PG), R1.1
unnamed: IC1.5 (SW), L1.1
unnamed: J2.A5 (CC1), R5.1
unnamed: J2.B5 (CC2), R4.1
unnamed: C10.1, R13.2, S1.2 (NO), U1.4 (IO0)
unnamed: C12.1, R17.2, S2.2 (NO), U1.45 (EN)
RGB: D6.3 (DIN), U1.30 (IO48)
RX: J6.3, U1.40 (RXD0)
SCL: J3.4, R14.2, U1.13 (IO9), U4.1 (SCL)
SDA: J3.3, R16.2, U1.12 (IO8), U4.6 (SDA)
TX: J6.4, U1.39 (TXD0)
VSYS: C5.1, IC1.1 (EN), IC1.6 (VIN), R1.2, U2.6 (VOUT), U3.6 (VOUT)
V_USB: C9.1, D1.1 (A1), J2.A4 (VBUS_1), J2.A9 (VBUS_2), J2.B4 (VBUS_3), J2.B9 (VBUS_4), R11.1, U2.1 (VIN), U3.3 (~CE)

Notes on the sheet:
Voltage Regulator 3.3V
Boot Mode
ESP32-S3-MINI
Power Switch Reverse Current Protection
Temperature
RGB LED & LED
Reset
Enable internal pull up for alert
B6 A6 DP B7 A7 DN B5 CC2 pull low A5 CC1 pull low A4 A9 B4 B9 VBUS A1 A12 B1 B12 GND A8 B8 NC
USB C Connector with ESD
QWIIC
